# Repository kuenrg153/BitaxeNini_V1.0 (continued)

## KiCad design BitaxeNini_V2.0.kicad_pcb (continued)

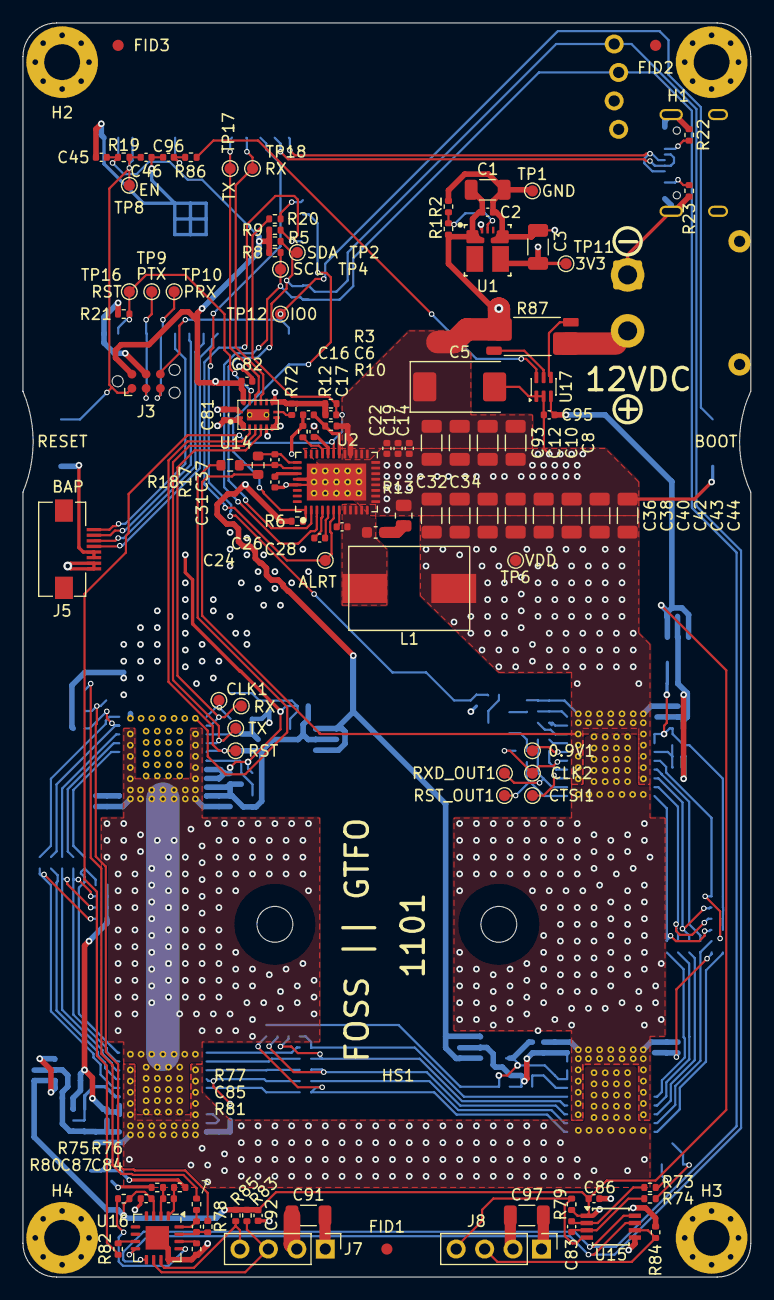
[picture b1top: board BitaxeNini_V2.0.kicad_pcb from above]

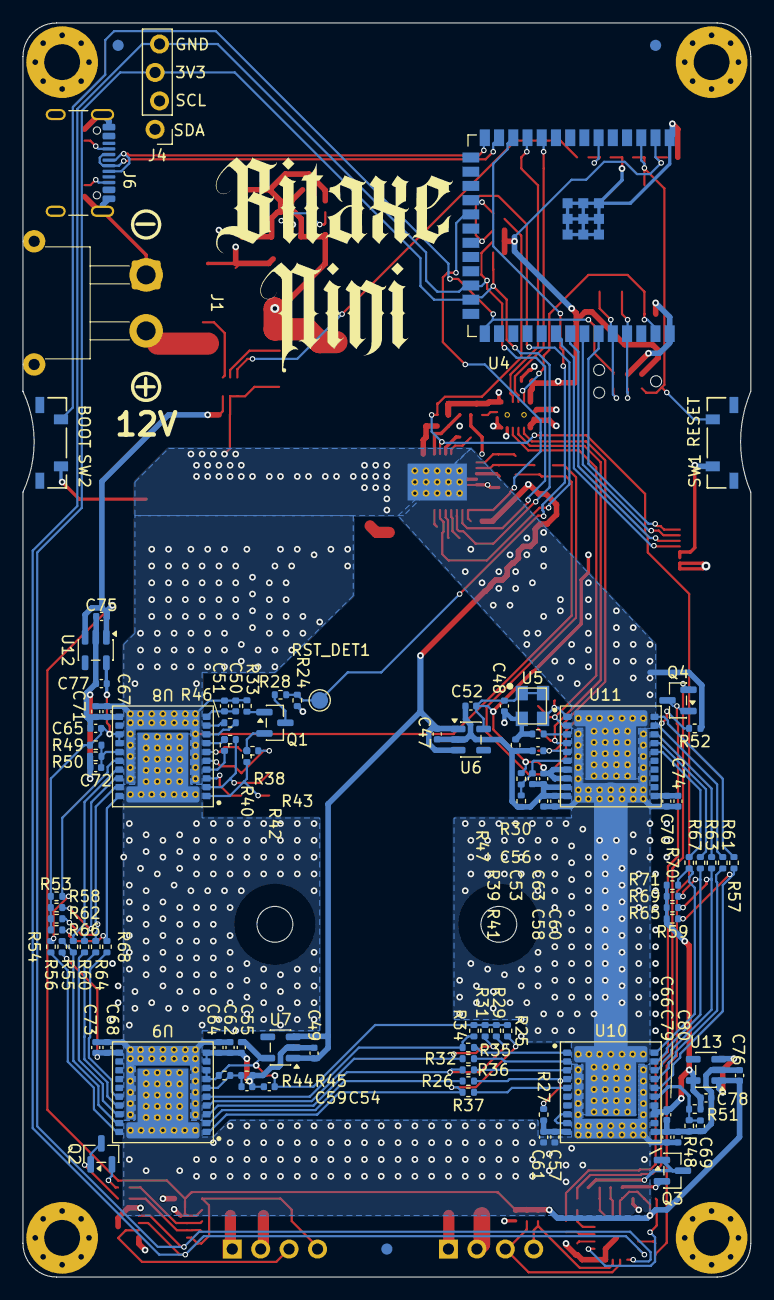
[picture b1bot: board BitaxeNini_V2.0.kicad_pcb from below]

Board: 4 copper layers, 65.0 x 112.0 mm, 219 parts (103 on the bottom side), 131 nets.

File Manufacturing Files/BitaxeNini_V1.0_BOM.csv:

Item,Qty,Reference,Value,Footprint,Manufacturer Part Number,DigiKey Part Number,Notes
1,8,"C1,C3,C8,C10,C12,C91,C93,C97",22uF,Capacitor_SMD:C_1206_3216Metric,CL31A226KAHNNNE,1276-3047-1-ND,
2,19,"C2,C6,C26,C48,C51,C53,C55,C56,C59,C63,C65,C66,C69,C72,C81,C82,C86,C87,C92",0.1uF,Capacitor_SMD:C_0402_1005Metric,GRM155R71E104KE14D,490-10698-1-ND,
3,1,C5,33uF,Capacitor_Tantalum_SMD:CP_EIA-7343-31_Kemet-D,T495D336K025ATE300,399-3882-1-ND,
4,13,"C16,C24,C46,C47,C49,C52,C54,C75,C76,C77,C78,C95,C96",1uF,Capacitor_SMD:C_0402_1005Metric,GRM155R61E105KA12D,490-10017-1-ND,
5,1,C17,4.7uF,Capacitor_SMD:C_0402_1005Metric,GRM155R61A475MEAAD,490-14306-1-ND,
6,2,"C19,C22",4.7nF,Capacitor_SMD:C_0402_1005Metric,GRM155R71E472KA01D,490-1309-1-ND,
7,1,C28,1000pF,Capacitor_SMD:C_0603_1608Metric,CC0603KRX7R9BB102,311-1080-1-ND,Corrected from 0805 part no. to match the 0603 footprint
8,1,C31,33pF,Capacitor_SMD:C_0402_1005Metric,KGM05ACG1E330JH,478-KGM05ACG1E330JHCT-ND,
9,8,"C32,C34,C36,C38,C40,C42,C43,C44",100uF,Capacitor_SMD:C_1206_3216Metric,CL31A107MQHNNNE,1276-1782-1-ND,
10,1,C37,100pF,Capacitor_SMD:C_0402_1005Metric,CC0402JRNPO9BN101,311-1024-1-ND,
11,15,"C45,C57,C58,C60,C61,C62,C64,C67,C68,C70,C71,C73,C74,C79,C80",10uF,Capacitor_SMD:C_0402_1005Metric,GMC04X5R106M6R3NT,2571-GMC04X5R106M6R3NTTR-ND,"DigiKey Marketplace (Cal-Chip), tape & reel only, 10k MOQ - substitute any 10uF 6.3V X5R 0402 for small builds"
12,3,"C83,C84,C85",470pF,Capacitor_SMD:C_0402_1005Metric,CC0402KRX7R9BB471,311-1028-1-ND,
13,1,J1,Screw_Terminal_01x02,"TerminalBlock_Phoenix:TerminalBlock_Phoenix_MKDS-1,5-2_1x02_P5.00mm_Horizontal",1729128,277-1247-ND,"MKDSN 1,5/2-5,08 (5.08 mm) fits the 5.0 mm footprint (1.3 mm holes). Through-hole"
14,1,J5,Conn_01x08,bitaxe:FPC-SMD_P0.50-8P_FGS-XJ-H2.0,FFC2B35-08-T,2073-FFC2B35-08-TCT-ND,
15,1,J6,USB_C_Receptacle_USB2.0,bitaxe:USB_C_Receptacle_GCT_USB4105-xx-A,USB4105-GF-A,2073-USB4105-GF-ACT-ND,
16,2,"J7,J8",Conn_01x04,Connector_PinHeader_2.54mm:PinHeader_1x04_P2.54mm_Vertical,0470531000,WM4330-ND,
17,1,L1,270nH,bitaxe:SLC1175-271MEC_COC,SLC1175-271MEC,,Coilcraft - not stocked at DigiKey; buy direct (coilcraft.com) or Mouser 994-SLC1175-271MEC
18,4,"Q1,Q2,Q3,Q4",MMBT3906,Package_TO_SOT_SMD:SOT-23,MMBT3906LT1G,MMBT3906LT1GOSCT-ND,
19,12,"R1,R3,R6,R19,R21,R24,R28,R33,R72,R79,R85,R86",10k,Resistor_SMD:R_0402_1005Metric,RC0402FR-0710KL,311-10.0KLRCT-ND,
20,6,"R2,R5,R8,R9,R22,R23",5.1k,Resistor_SMD:R_0402_1005Metric,RC0402FR-075K1L,311-5.10KLRCT-ND,
21,1,R10,10,Resistor_SMD:R_0402_1005Metric,RC0402FR-0710RL,311-10.0LRCT-ND,
22,1,R13,1,Resistor_SMD:R_0805_2012Metric,ESR10EZPJ1R0,RHM1KTR-ND,
23,2,"R17,R18",49.9,Resistor_SMD:R_0603_1608Metric,RC0603FR-0749R9L,311-49.9HRCT-ND,
24,2,"R20,R81",2.2k,Resistor_SMD:R_0402_1005Metric,RC0402FR-072K2L,311-2.20KLRCT-ND,
25,6,"R25,R31,R53,R59,R62,R69",402,Resistor_SMD:R_0402_1005Metric,RC0402FR-07402RL,311-402LRCT-ND,
26,9,"R26,R35,R36,R55,R60,R61,R63,R68,R70",200,Resistor_SMD:R_0402_1005Metric,RC0402FR-07200RL,311-200LRCT-ND,
27,3,"R27,R52,R56",560,Resistor_SMD:R_0402_1005Metric,RC0402FR-07560RL,311-560LRCT-ND,
28,7,"R29,R34,R40,R58,R65,R66,R71",1k,Resistor_SMD:R_0402_1005Metric,RC0402FR-071KL,311-1.00KLRCT-ND,
29,4,"R30,R42,R47,R82",0,Resistor_SMD:R_0402_1005Metric,RC0402JR-070RL,311-0.0JRCT-ND,
30,9,"R32,R64,R67,R73,R74,R75,R76,R77,R78",100,Resistor_SMD:R_0402_1005Metric,RC0402FR-07100RL,311-100LRCT-ND,
31,7,"R37,R39,R44,R49,R51,R54,R57",33,Resistor_SMD:R_0402_1005Metric,RC0402FR-0733RL,311-33.0LRCT-ND,
32,4,"R41,R45,R48,R50",27,Resistor_SMD:R_0402_1005Metric,RC0402FR-0727RL,311-27.0LRCT-ND,
33,3,"R80,R83,R84",6.8k,Resistor_SMD:R_0402_1005Metric,RC0402FR-076K8L,311-6.80KLRCT-ND,
34,1,R87,5mOhm,Resistor_SMD:R_Shunt_Vishay_WSK2512_6332Metric_T1.19mm,WSK25125L000FEA,541-WSK25125L000FEATR-ND,
35,2,"SW1,SW2",SWITCH-SPST,bitaxe:SW_TL3330AF130QG_EWI,TL3330AF130QG,EG4388CT-ND,
36,1,U1,TPSM861253RDXR,bitaxe:TPSM863257RDX,TPSM861253RDXR,296-TPSM861253RDXRCT-ND,Footprint named TPSM863257RDX (same RDX package)
37,1,U2,TPS546D24S,bitaxe:LQFN40-CLIP,TPS546D24SRVFR,296-TPS546D24SRVFRCT-ND,
38,1,U4,ESP32-S3-WROOM-1,bitaxe:ESP32-S3-WROOM-1,ESP32-S3-WROOM-1-N16R8,1965-ESP32-S3-WROOM-1-N16R8CT-ND,Mounted on BOTTOM side
39,1,U5,24MHz,bitaxe:SMD3225-4P,SX3M24.000E20F30THN,5852-SX3M24.000E20F30THNTR-ND,
40,4,"U6,U7,U12,U13",LP5907MFX-1.8,Package_TO_SOT_SMD:SOT-23-5,LP5907MFX-1.8/NOPB,296-41463-1-ND,
41,4,"U8,U9,U10,U11",KF1950,bitaxe:KF1950,KF1950,,Bitcoin ASIC - not available at DigiKey; customer-supplied (consigned). Mounted on BOTTOM side
42,1,U14,SN74AVC4T774,bitaxe:BQB0016A-MFG,SN74AXC4T774BQBR,296-SN74AXC4T774BQBRCT-ND,
43,1,U15,EMC2101,Package_SO:TSSOP-8_3x3mm_P0.65mm,EMC2101-R-ACZL-TR,EMC2101-R-ACZL-CT-ND,
44,1,U16,EMC2103-2,Package_DFN_QFN:QFN-16-1EP_4x4mm_P0.65mm_EP2.1x2.1mm,EMC2103-2-AP-TR,EMC2103-2-AP-CT-ND,EMC2103-2 variant required (the -4 adds an EEPROM interface - not used)
45,1,U17,NCS21671SQ050T2G,Package_TO_SOT_SMD:SOT-363_SC-70-6,NCS21671SQ050T2G,488-NCS21671SQ050T2GCT-ND,
